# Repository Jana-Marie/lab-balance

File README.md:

# lab-balance

This project aims to replace the electronics contained within a [cheap scale from AliExpress](https://aliexpress.com/item/33024586342.html) to archive a higher resolution and hackability. Furthermore I need a scale which does not turn off after 30 seconds of use!

The goal is not met so far, as the accuracy of the load cell is not sufficient for this task. It can be replaced with a higher end model.

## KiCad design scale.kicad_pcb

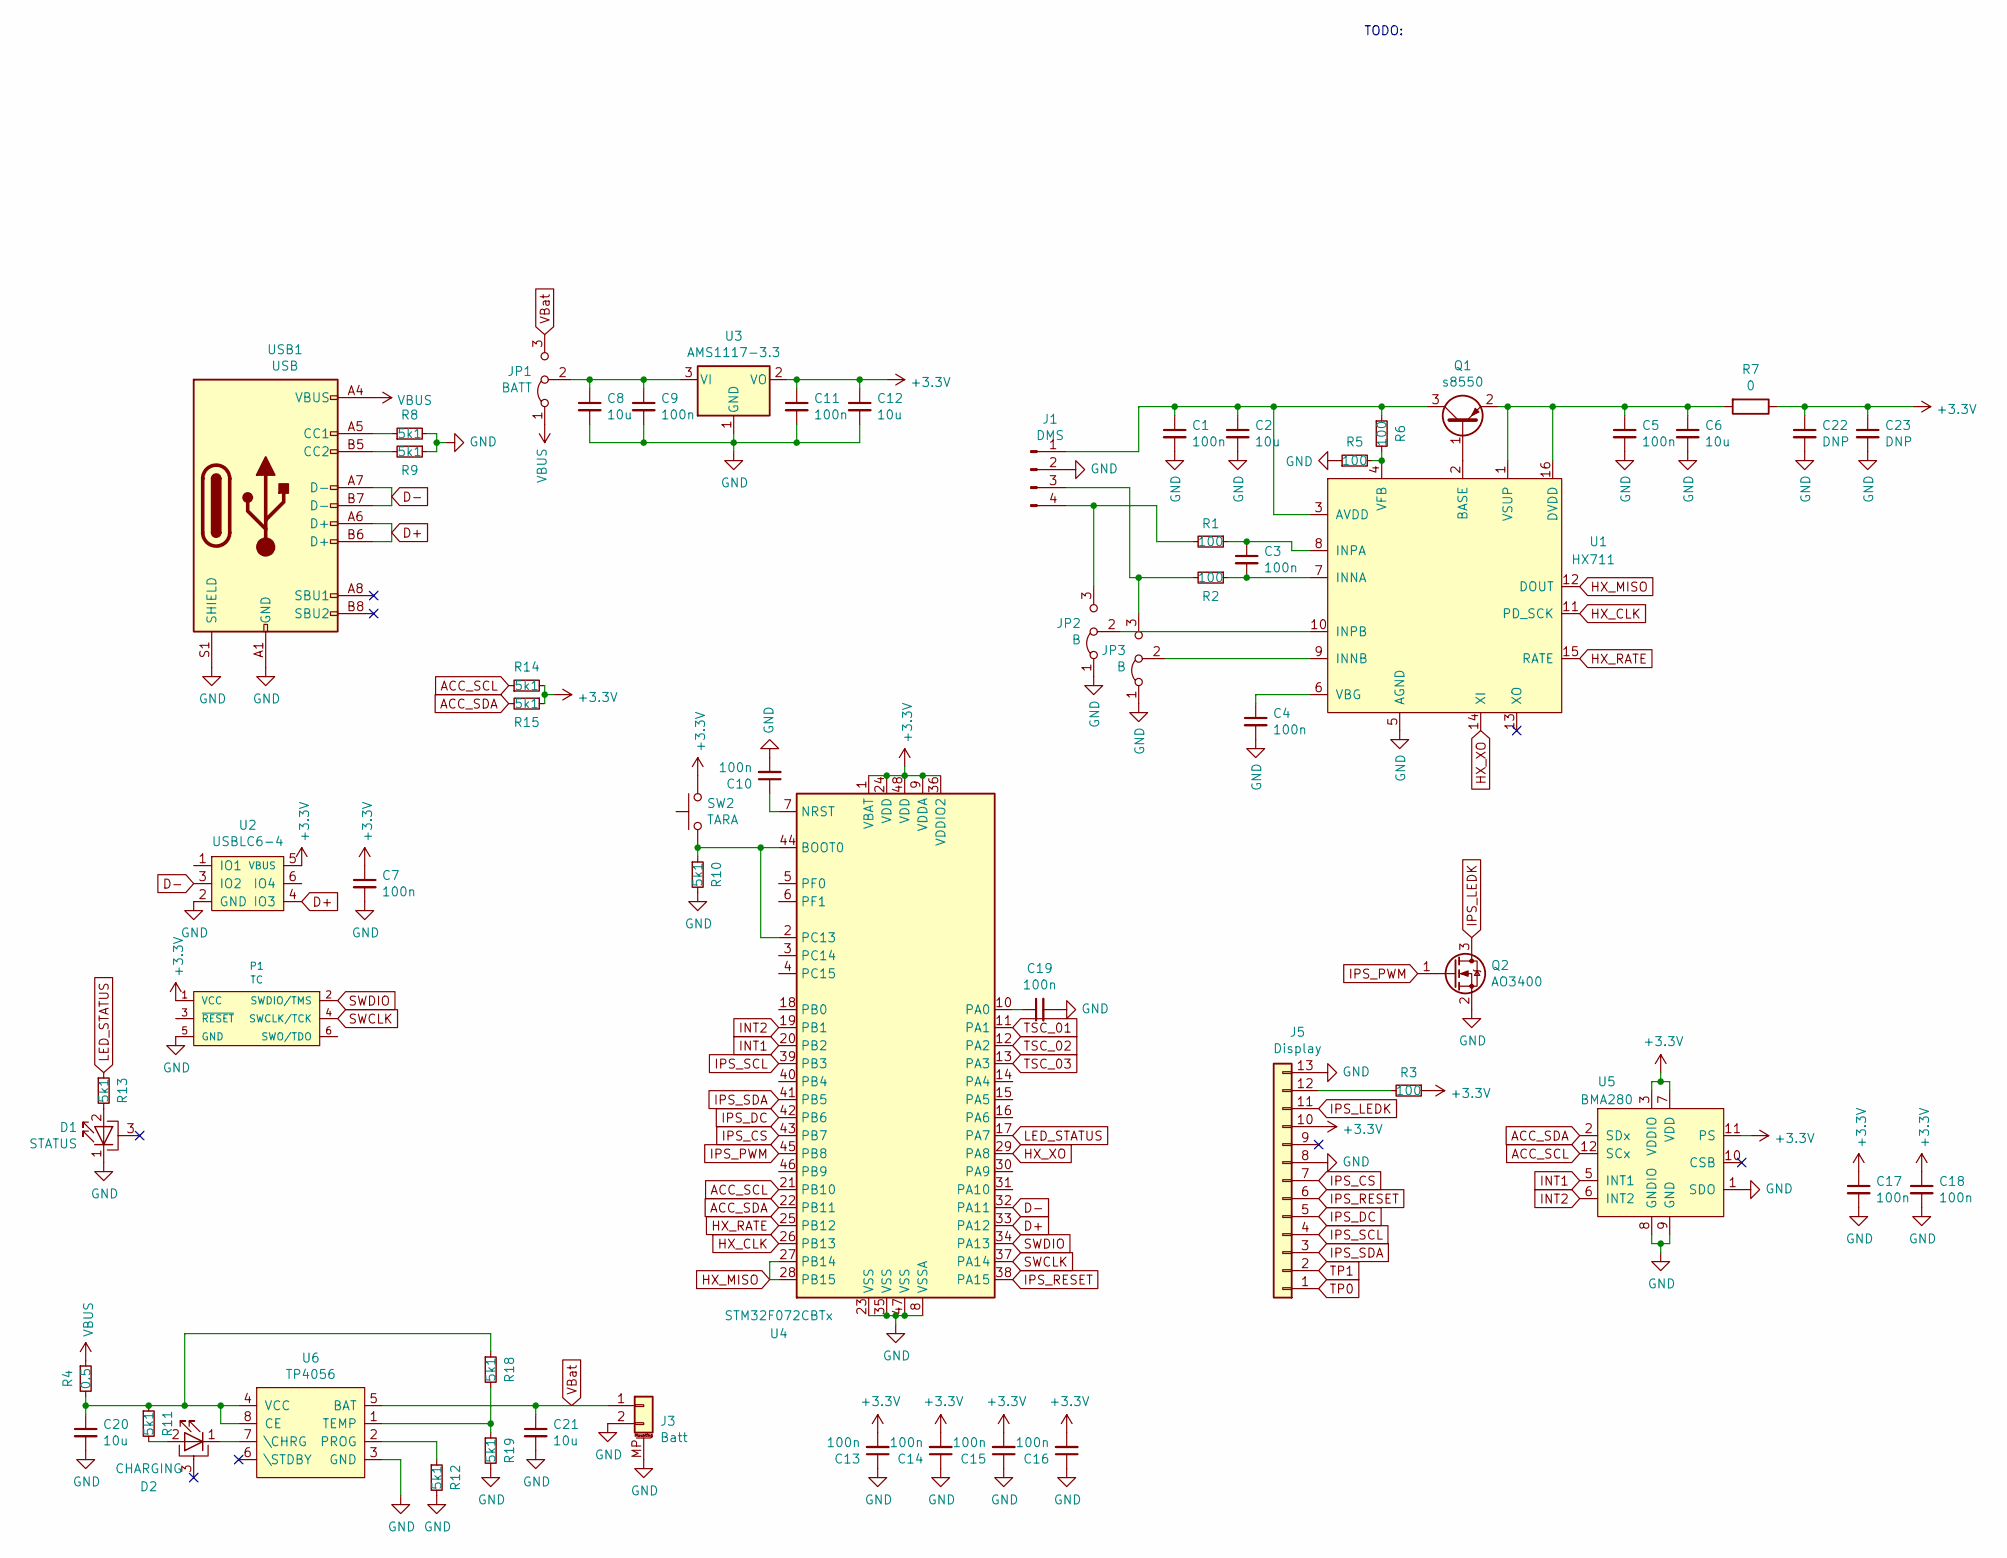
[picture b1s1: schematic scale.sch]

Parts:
C1, C3, C4, C5, C7, C9, C10, C11, C13, C14, C15, C16, C17, C18, C19: 100n; C_0603
C2, C6, C8, C12, C20, C21: 10u; C_0603
C22, C23: DNP; C_0603
D1: STATUS; BL-HUB34E-AV-TRB
D2: CHARGING; BL-HUB34E-AV-TRB
J1: DMS; 04_pads
J3: Batt; JST_GH_SM02B-GHS-TB_1x02-1MP_P1.25mm_Horizontal
J5: Display; 0.96IPS
JP1: BATT; J_0603_90
JP2, JP3: B; J_0603_90
P1: TC; TC2030
Q1: s8550; SOT-23
Q2: AO3400; SOT-23
R1, R2, R3, R5, R6: 100; R_0603
R4: 0.5; R_0805
R7: 0; R_0805
R8, R9, R10, R11, R12, R13, R14, R15, R18, R19: 5k1; R_0603
SW2: TARA; K2-1102DP-C4SW-04
U1: HX711; SOIC-16_3.9x9.9mm_P1.27mm
U2: USBLC6-4; SOT-23-6
U3: AMS1117-3.3; SOT-223-3_TabPin2
U4: STM32F072CBTx; LQFP-48_7x7mm_P0.5mm
U5: BMA280; LGA-12_2x2mm_P0.5mm
U6: TP4056; SOP-8_3.9x4.9mm_P1.27mm
USB1: USB; USB-C 16Pin

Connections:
+3V3: C7.1, C11.1, C12.1, C13.2, C14.2, C15.2, C16.2, C17.1, C18.1, C22.1, C23.1, J5.10, P1.1 (VCC), R3.1, R7.1, R14.2, R15.1, SW2.2, U2.5 (VBUS), U3.2 (VO), U4.1 (VBAT), U4.9 (VDDA), U4.24 (VDD), U4.36 (VDDIO2), U4.48 (VDD), U5.3 (VDDIO), U5.7 (VDD), U5.11 (PS)
ACC_SCL: R14.1, U4.21 (PB10), U5.12 (SCx)
ACC_SDA: R15.2, U4.22 (PB11), U5.2 (SDx)
D+: U2.4 (IO3), U4.33 (PA12), USB1.A6 (D+), USB1.B6 (D+)
D-: U2.3 (IO2), U4.32 (PA11), USB1.A7 (D-), USB1.B7 (D-)
GND: C1.2, C2.2, C4.2, C5.2, C6.2, C7.2, C8.2, C9.2, C10.2, C11.2, C12.2, C13.1, C14.1, C15.1, C16.1, C17.2, C18.2, C19.2, C20.2, C21.2, C22.2, C23.2, D1.1 (K), J1.2, J3.2, J3.MP (MountPin), J5.8, J5.13, JP2.1 (A), JP3.1 (A), P1.5 (GND), Q2.2 (S), R5.1, R8.2, R9.1, R10.2, R12.2, R19.2, U1.5 (AGND), U2.2 (GND), U3.1 (GND), U4.8 (VSSA), U4.23 (VSS), U4.35 (VSS), U4.47 (VSS), U5.1 (SDO), U5.8 (GNDIO), U5.9 (GND), U6.3 (GND), USB1.A1 (GND), USB1.A12 (GND), USB1.B1 (GND), USB1.B12 (GND), USB1.S1 (SHIELD)
HX_CLK: U1.11 (PD_SCK), U4.26 (PB13)
HX_MISO: U1.12 (DOUT), U4.27 (PB14), U4.28 (PB15)
HX_RATE: U1.15 (RATE), U4.25 (PB12)
HX_XO: U1.14 (XI), U4.29 (PA8)
INT1: U4.20 (PB2), U5.5 (INT1)
INT2: U4.19 (PB1), U5.6 (INT2)
IPS_CS: J5.7, U4.43 (PB7)
IPS_DC: J5.5, U4.42 (PB6)
IPS_LEDK: J5.11, Q2.3 (D)
IPS_PWM: Q2.1 (G), U4.45 (PB8)
IPS_RESET: J5.6, U4.38 (PA15)
IPS_SCL: J5.4, U4.39 (PB3)
IPS_SDA: J5.3, U4.41 (PB5)
LED_STATUS: R13.1, U4.17 (PA7)
unnamed: C1.1, C2.1, J1.1, Q1.3 (C), R6.1, U1.3 (AVDD)
unnamed: C3.1, R1.1, U1.8 (INPA)
unnamed: C3.2, R2.1, U1.7 (INNA)
unnamed: C4.1, U1.6 (VBG)
unnamed: C5.1, C6.1, Q1.2 (E), R7.2, U1.1 (VSUP), U1.16 (DVDD)
unnamed: C8.1, C9.1, JP1.2 (C), U3.3 (VI)
unnamed: C10.1, U4.7 (NRST)
unnamed: C19.1, U4.10 (PA0)
unnamed: C20.1, R4.2, R11.1, R18.1, U6.4 (VCC), U6.8 (CE)
unnamed: D1.2 (A), R13.2
unnamed: D2.1 (K), U6.7 (\CHRG)
unnamed: D2.2 (A), R11.2
unnamed: J1.3, JP3.3 (B), R2.2
unnamed: J1.4, JP2.3 (B), R1.2
unnamed: J5.12, R3.2
unnamed: JP2.2 (C), U1.10 (INPB)
unnamed: JP3.2 (C), U1.9 (INNB)
unnamed: Q1.1 (B), U1.2 (BASE)
unnamed: R5.2, R6.2, U1.4 (VFB)
unnamed: R8.1, USB1.A5 (CC1)
unnamed: R9.2, USB1.B5 (CC2)
unnamed: R10.1, SW2.1, U4.2 (PC13), U4.44 (BOOT0)
unnamed: R12.1, U6.2 (PROG)
unnamed: R18.2, R19.1, U6.1 (TEMP)
SWCLK: P1.4 (SWCLK/TCK), U4.37 (PA14)
SWDIO: P1.2 (SWDIO/TMS), U4.34 (PA13)
TP0: J5.1
TP1: J5.2
TSC_01: U4.11 (PA1)
TSC_02: U4.12 (PA2)
TSC_03: U4.13 (PA3)
VBUS: JP1.1 (A), R4.1, USB1.A4 (VBUS), USB1.A9 (VBUS), USB1.B4 (VBUS), USB1.B9 (VBUS)
VBat: C21.1, J3.1, JP1.3 (B), U6.5 (BAT)

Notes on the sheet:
TODO:

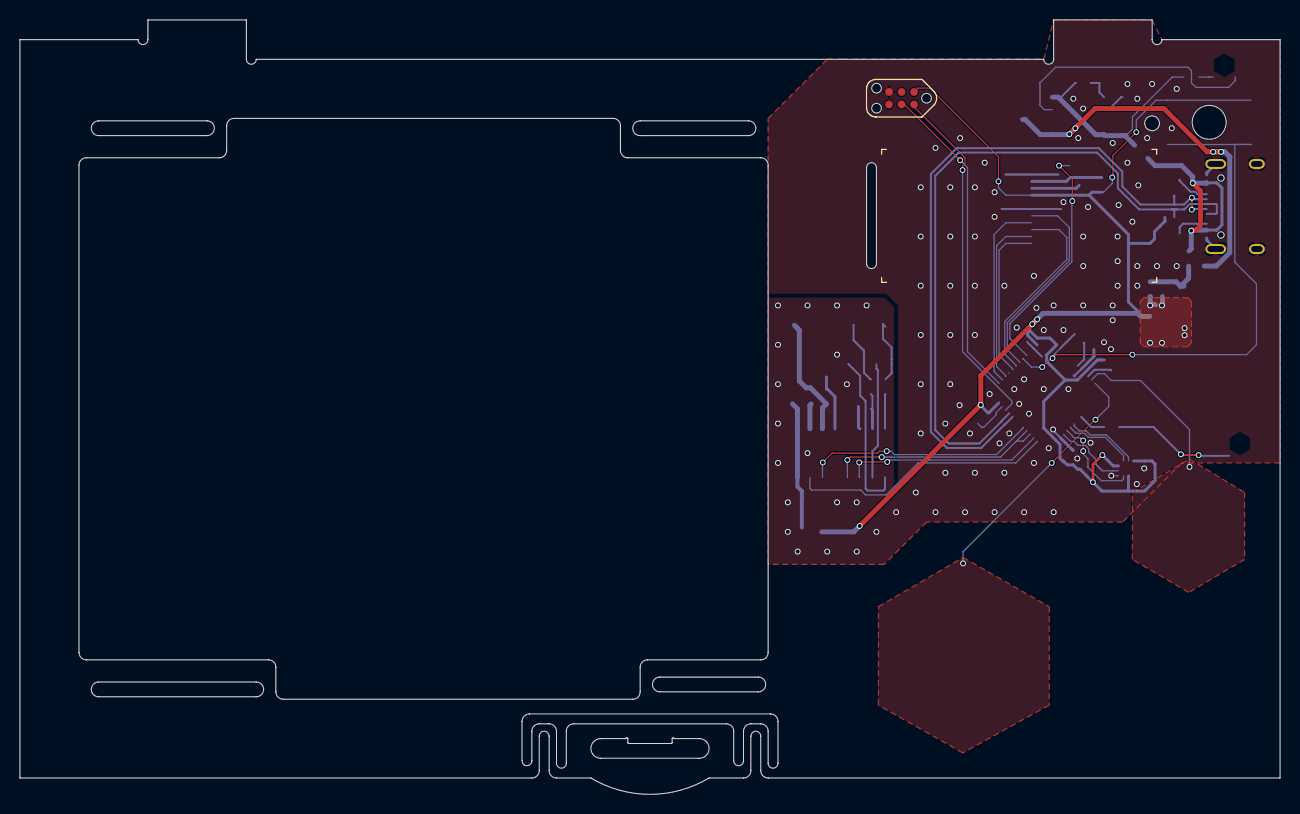
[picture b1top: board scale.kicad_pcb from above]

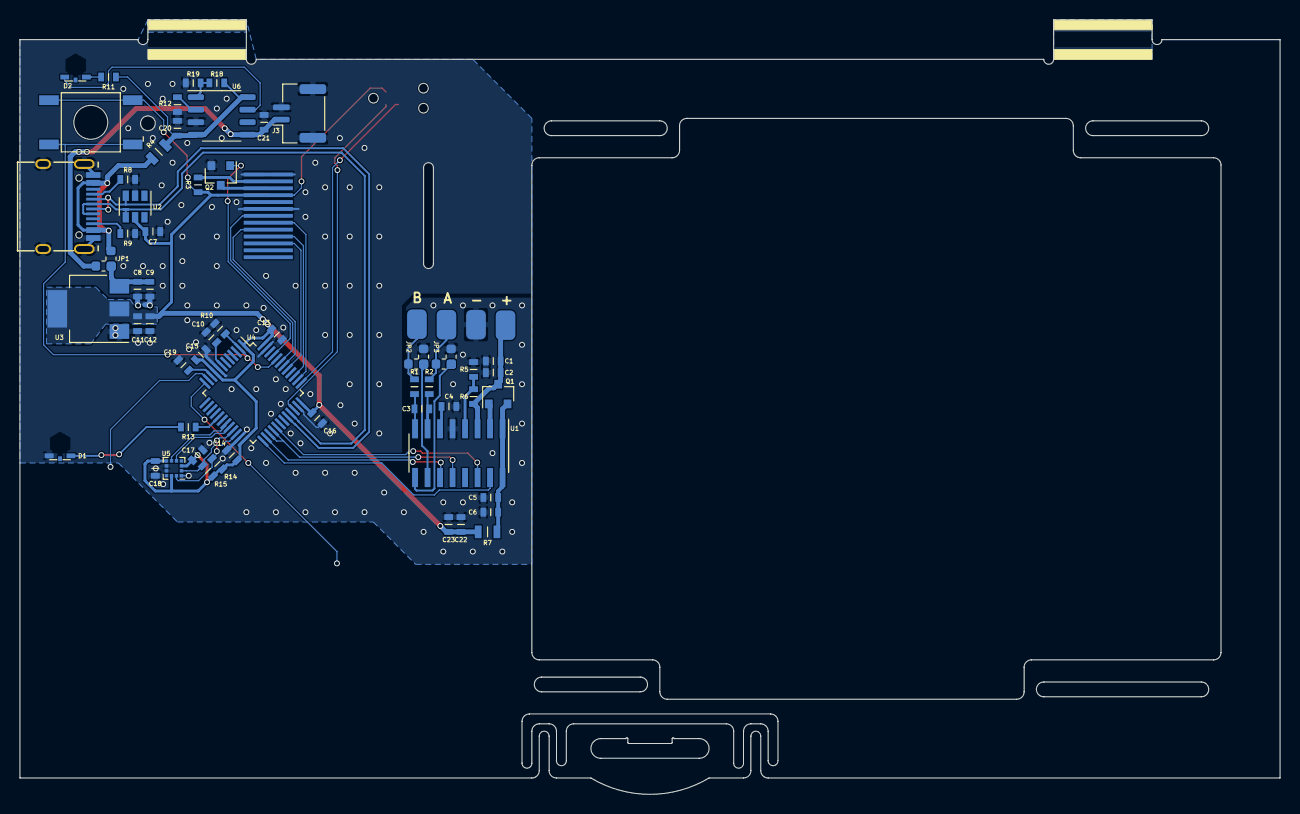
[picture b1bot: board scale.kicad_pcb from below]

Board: 2 copper layers, 128.0 x 78.7 mm, 59 parts (57 on the bottom side), 48 nets.

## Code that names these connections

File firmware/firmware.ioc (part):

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Mcu.Name=STM32F072C(8-B)Tx
Mcu.Package=LQFP48
Mcu.UserName=STM32F072CBTx
PA0.Mode=G1_IO1-Sampling
PA0.Signal=TSC_G1_IO1
PA1.Mode=G1_IO2-Channel
PA1.Signal=TSC_G1_IO2
PA11.Mode=Device
PA11.Signal=USB_DM
PA12.Mode=Device
PA12.Signal=USB_DP
PA13.Mode=Serial_Wire
PA13.Signal=SYS_SWDIO
PA14.Mode=Serial_Wire
PA14.Signal=SYS_SWCLK
PA15.GPIOParameters=GPIO_Label
PA15.GPIO_Label=IPS_RESET
PA15.Signal=GPIO_Output
PA2.Mode=G1_IO3-Channel
PA2.Signal=TSC_G1_IO3
PA7.GPIOParameters=GPIO_Label
PA7.GPIO_Label=LED
PA7.Signal=GPIO_Output
PA8.Signal=S_TIM1_CH1
PB1.GPIOParameters=GPIO_Label
PB1.GPIO_Label=ACC_INT1
PB1.Signal=GPXTI1
PB10.GPIOParameters=GPIO_Label
PB10.GPIO_Label=ACC_SCL
PB10.Mode=I2C
PB10.Signal=I2C2_SCL
PB11.GPIOParameters=GPIO_Label
PB11.GPIO_Label=ACC_SDA
PB11.Mode=I2C
PB11.Signal=I2C2_SDA
PB12.GPIOParameters=GPIO_Label
PB12.GPIO_Label=HX_SPS
PB12.Signal=GPIO_Output
PB13.GPIOParameters=GPIO_Label
PB13.GPIO_Label=HX_CLK
PB13.Signal=GPIO_Output
PB14.GPIOParameters=GPIO_Label
PB14.GPIO_Label=HX_DATA
PB14.Signal=GPIO_Input
PB15.GPIOParameters=GPIO_Label
PB15.GPIO_Label=HX_INT
PB15.Signal=GPXTI15
PB2.GPIOParameters=GPIO_Label
PB2.GPIO_Label=ACC_INT2
PB2.Signal=GPXTI2
PB3.GPIOParameters=GPIO_Label
PB3.GPIO_Label=IPS_SCK
PB3.Mode=TX_Only_Simplex_Unidirect_Master
PB3.Signal=SPI1_SCK
PB5.GPIOParameters=GPIO_Label
PB5.GPIO_Label=IPS_MOSI
PB5.Mode=TX_Only_Simplex_Unidirect_Master
PB5.Signal=SPI1_MOSI
PB6.GPIOParameters=GPIO_Label
PB6.GPIO_Label=IPS_DC
PB6.Signal=GPIO_Output
PB7.GPIOParameters=GPIO_Label
PB7.GPIO_Label=IPS_CS
PB7.Signal=GPIO_Output
PB8.GPIOParameters=GPIO_Label
PB8.GPIO_Label=IPS_PWM
PB8.Signal=S_TIM16_CH1
PC13.GPIOParameters=GPIO_Label
PC13.GPIO_Label=DFU
PC13.Signal=GPIO_Input
RCC.SYSCLKFreq_VALUE=48000000
RCC.SYSCLKSource=RCC_SYSCLKSOURCE_HSI48
board=custom

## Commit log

2020-03-01 added gitignore
2020-03-01 added files
2020-03-01 push
2020-03-02 added gerber
2020-03-02 pushed latest files
2020-04-03 added firmware
2020-04-15 firmware 01
2020-06-07 calibrated load cell
2020-06-08 pushed files
2020-06-08 added images
2020-06-08 added binaries
2020-06-08 removed binarie
2020-11-08 added bmps and converter
2020-11-08 updated pngs and converter
2020-11-08 added png write
2020-11-08 removed old images
2020-11-08 updated ui
2020-11-08 added includes
2020-11-08 added more images
2020-11-08 fixed pointer types
2020-11-08 added flash + USB
2020-11-08 added usb
2020-11-08 removed USB
2020-11-08 added serial, but buggy
